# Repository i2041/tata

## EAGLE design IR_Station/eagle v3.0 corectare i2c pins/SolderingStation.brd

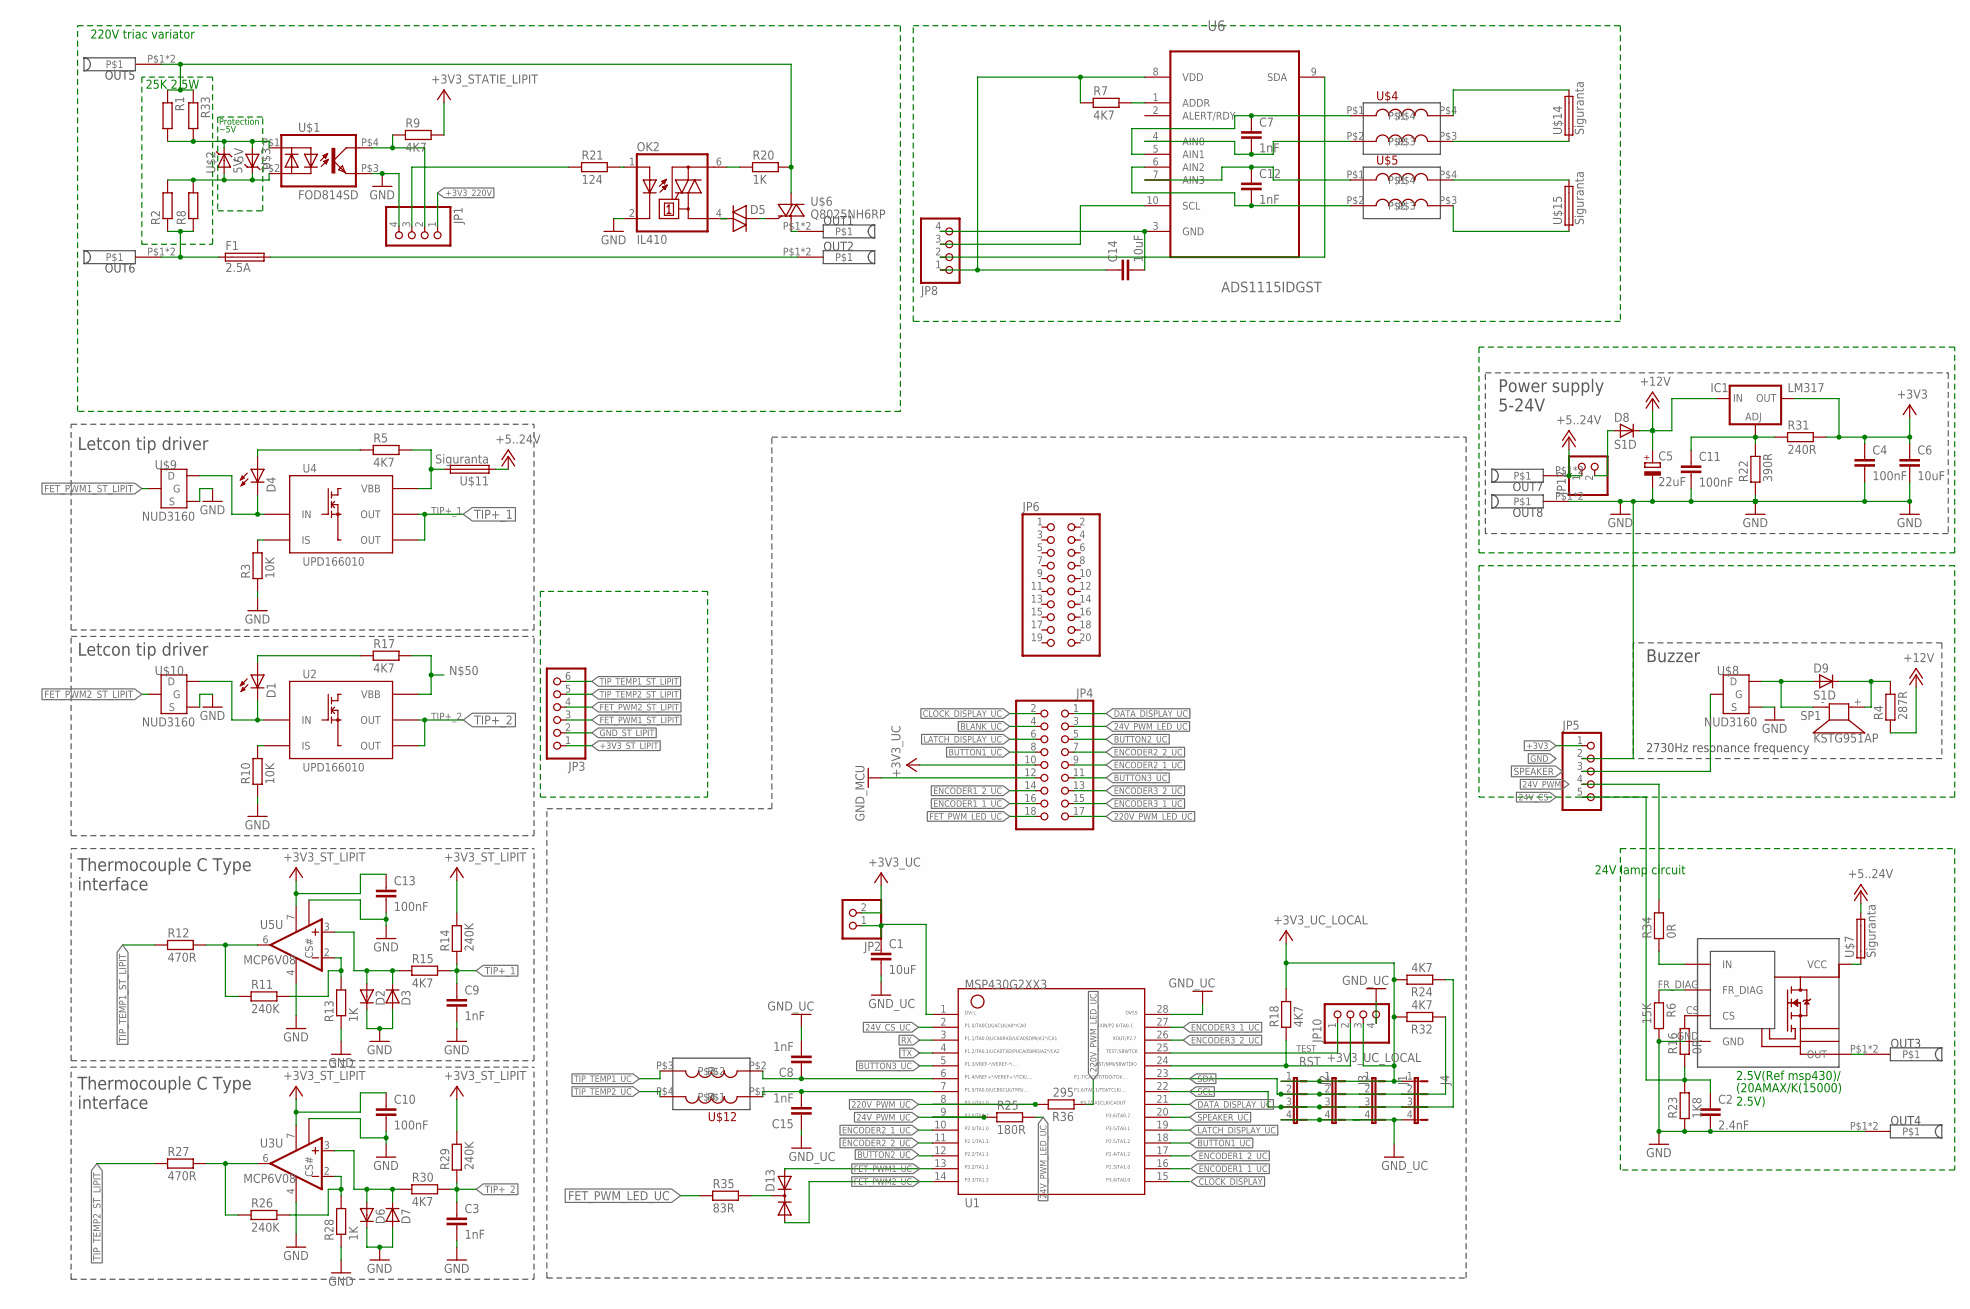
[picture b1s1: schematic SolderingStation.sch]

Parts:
C1, C6: 10uF; 1206
C2: 2.4nF; 0805
C3, C7, C8, C9, C12, C15: 1nF; 0805
C4, C11: 100nF; 1206
C5: 22uF; C_EL_6.3X5.4
C10, C13: 100nF; 0805
C14: 10uF; 0805
CLH1: VN7004; OCTAPAK
D1, D4: LED3MM; LED_3MM
D2, D3, D6, D7: DIODES1D; S1D
D5: DIAC-DO35-10; DO35-10
D8, D9: S1D
D13: DIODE-2AC|CASOT23; SOT23
F1: 2.5A; GSH15
IC1: LM317; DPACK
J1, J2, J3, J4: JP4
JP1, JP8: PINHD-1X4/90; 1X04/90
JP2, JP12: PINHD-1X2; 1X02
JP3: PINHD-1X6/90; 1X06/90
JP4: PINHD-2X9; 2X09
JP5: PINHD-1X5/90; 1X05/90
JP6: PINHD-2X10/90; 2X10/90
JP10: PINHD-1X4; 1X04
OK2: IL410; DIL06
OUT1, OUT2, OUT3, OUT4, OUT5, OUT6, OUT7, OUT8: BANANA
R1, R2, R8, R33: RESISTOR-PTH-0.4; RTH025W
R3, R10: 10K; 0805
R4: 287R; 1206
R5, R7, R15, R17, R18, R24, R30, R32: 4K7; 0805
R6: 15K; 0805
R9: 4K7; 1206
R11, R14, R26, R29: 240K; 0805
R12, R27: 470R; 0805
R13, R28: 1K; 0805
R16, R34: 0R; 0805
R20: 1K; 1206
R21: 124; 1206
R22: 390R; 0805
R23: 1K8; 0805
R25: 180R; 0805
R31: 240R; 0805
R35: 83R; 0805
R36: 295; 1206
SP1: KSTG951AP
U1: MSP340G2443; PW28
U2, U4: UPD166010; TO252-51
U3, U5: MCP6V08; SO08
U6: ADS1115IDGST; SOP50P490X110-10N
U$1: FOD814SD; DIP_4PIN
U$2, U$3: 5V; ZENER
U$4, U$5, U$12: COIL; UNDEF1
U$6: Q8025NH6RP; TO-263
U$7, U$11, U$14, U$15: Siguranta; SOCLU_THERMOCOUPLE
U$8, U$9, U$10: NUD3160; SOT23

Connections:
24V_CS: C2.1, JP5.5, R16.1, R23.2
24V_CS_UC: U1.2
24V_PWM: JP5.4, R34.2
24V_PWM_LED_UC: JP4.3, R25.2
24V_PWM_UC: R25.1, U1.9
220V_PWM_LED_UC: JP4.17, R36.1
220V_PWM_UC: R36.2, U1.8
+3V3: C4.1, C6.1, IC1.4 (OUT), JP5.1, R31.2
+3V3_220V: JP1.1, R9.2
+3V3_ST_LIPIT: C10.1, C13.1, JP3.1, R14.2, R29.2, U3.7 (V+), U5.7 (V+)
+3V3_UC: JP2.2, JP4.10
+3V3_UC_LOCAL: C1.1, J1.1, J2.1, J3.1, J4.1, JP2.1, JP10.3, R18.2, R24.2, R32.2, U1.1
+12V: C5.+, D8.C, IC1.3 (IN), R4.1
+15V: JP12.1, OUT7.P$1, OUT7.P$2, U$7.1B (2), U$7.2B (2), U$11.1A (1), U$11.2A (1)
BLANK_UC: JP4.4
BUTTON1_UC: JP4.8, U1.18
BUTTON2_UC: JP4.5, U1.12
BUTTON3_UC: JP4.11, U1.5
CLOCK_DISPLAY: U1.15
CLOCK_DISPLAY_UC: JP4.2
DATA_DISPLAY_UC: JP4.1, U1.21
ENCODER1_1_UC: JP4.16, U1.16
ENCODER1_2_UC: JP4.14, U1.17
ENCODER2_1_UC: JP4.9, U1.10
ENCODER2_2_UC: JP4.7, U1.11
ENCODER3_1_UC: JP4.15, U1.27
ENCODER3_2_UC: JP4.13, U1.26
FET_PWM1_ST_LIPIT: JP3.3, U$9.1 (G)
FET_PWM1_UC: D13.2 (A2), U1.13
FET_PWM2_ST_LIPIT: JP3.4, U$10.1 (G)
FET_PWM2_UC: D13.1 (A1), U1.14
FET_PWM_LED_UC: JP4.18, R35.1
GND: C2.2, C4.2, C5.-, C6.2, C8.2, C11.2, C15.1, CLH1.GND, J2.4, J3.4, J4.4, JP5.2, OUT4.P$1, OUT4.P$2, OUT8.P$1, OUT8.P$2, R6.2, R22.1, R23.1, U$8.2 (S)
GND_220V: JP1.4, OK2.2 (C), U$1.P$3 (EMIT)
GND_ST_LIPIT: C3.2, C9.2, C10.2, C13.2, D2.C, D3.A, D6.C, D7.A, JP3.2, R3.1, R10.1, R13.1, R28.1, U3.4 (V-), U3.8 (CS#), U5.4 (V-), U5.8 (CS#), U$9.2 (S), U$10.2 (S)
GND_TERMOCOUPLE: C14.2, JP8.4, U6.3 (GND)
GND_UC: C1.2, JP4.12, JP10.4, U1.28
LATCH_DISPLAY_UC: JP4.6, U1.19
unnamed: D1.K (C), U2.2 (IN), U$10.3 (D)
unnamed: D4.A, R5.1
unnamed: D1.A, R17.1
unnamed: D9.A, SP1.- (2), U$8.3 (D)
unnamed: CLH1.CS, R16.2
unnamed: D4.K (C), U4.2 (IN), U$9.3 (D)
unnamed: R10.2, U2.4 (IS)
unnamed: R26.1, R27.2, U3.6 (OUT)
unnamed: D6.A, D7.C, R30.1, U3.3 (+IN)
unnamed: R26.2, R28.2, U3.2 (-IN)
unnamed: OK2.6 (A2), R20.1
unnamed: D5.A (1), OK2.4 (A1)
unnamed: OK2.1 (A), R21.2
unnamed: JP1.3, R21.1
unnamed: CLH1.VCC, U$7.1A (1), U$7.2A (1)
unnamed: D5.C (2), U$6.G
unnamed: D9.C, R4.2, SP1.+ (1)
unnamed: CLH1.FR_DIAG, R6.1
unnamed: F1.1, OUT6.P$1, OUT6.P$2, R2.1, R8.1
unnamed: R3.2, U4.4 (IS)
unnamed: D13.3 (C), R35.2
unnamed: R11.1, R12.2, U5.6 (OUT)
unnamed: R1.2, R33.2, U$1.P$1 (ANODE), U$2.K, U$3.A
unnamed: D2.A, D3.C, R15.1, U5.3 (+IN)
unnamed: R2.2, R8.2, U$1.P$2 (CATHODE), U$2.A, U$3.K
unnamed: R11.2, R13.2, U5.2 (-IN)
unnamed: CLH1.OUTPUT1 (OUT), CLH1.OUTPUT2 (OUT), CLH1.OUTPUT3 (OUT), OUT3.P$1, OUT3.P$2
unnamed: JP1.2, R9.1, U$1.P$4 (COL)
unnamed: C8.1, U1.6, U$12.P$2
unnamed: R7.2, U6.1 (ADDR)
unnamed: C15.2, U1.7, U$12.P$1
unnamed: C7.1, U6.5 (AIN1), U$4.P$1
unnamed: C7.2, U6.4 (AIN0), U$4.P$2
unnamed: C11.1, IC1.1 (ADJ), R22.2, R31.1
unnamed: C12.1, U6.7 (AIN3), U$5.P$1
unnamed: C12.2, U6.6 (AIN2), U$5.P$2
unnamed: CLH1.INPUT (IN), R34.1
unnamed: R5.2, R17.2, U2.TAB (VBB), U4.TAB (VBB), U$11.1B (2), U$11.2B (2)
unnamed: D8.A, JP12.2
unnamed: U$4.P$3, U$14.1A (1), U$14.2A (1)
unnamed: U$4.P$4, U$14.1B (2), U$14.2B (2)
unnamed: U$5.P$4, U$15.1B (2), U$15.2B (2)
unnamed: U$5.P$3, U$15.1A (1), U$15.2A (1)
RST: JP10.2, R18.1, U1.24
RX: U1.3
SCL: J1.3, J2.3, J3.3, J4.3, R24.1, U1.22
SCL_TERMOCOUPLE: JP8.3, U6.10 (SCL)
SDA: J1.2, J2.2, J3.2, J4.2, R32.1, U1.23
SDA_TERMOCOUPLE: JP8.2, U6.9 (SDA)
SPEAKER: JP5.3, U$8.1 (G)
SPEAKER_UC: U1.20
TEST: JP10.1, U1.25
TIP+_1: C9.1, R14.1, R15.2, U4.1 (OUT), U4.5 (OUT)
TIP+_2: C3.1, R29.1, R30.2, U2.1 (OUT), U2.5 (OUT)
TIP_TEMP1_ST_LIPIT: JP3.6, R12.1
TIP_TEMP1_UC: U$12.P$3
TIP_TEMP2_ST_LIPIT: JP3.5, R27.1
TIP_TEMP2_UC: U$12.P$4
TX: U1.4
VCC_TERMOCOUPLE: C14.1, JP8.1, R7.1, U6.8 (VDD)
~+OUT: F1.2, OUT2.P$1, OUT2.P$2
~-OUT: OUT1.P$1, OUT1.P$2, U$6.T1
~IN1: OUT5.P$1, OUT5.P$2, R1.1, R20.2, R33.1, U$6.T2

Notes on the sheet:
Letcon tip driver
Thermocouple C Type
interface
Power supply
5-24V
Buzzer
2730Hz resonance frequency
24V lamp circuit
220V triac variator
25K 2.5W
Protection
~5V
2.5V(Ref msp430)/
(20AMAX/K(15000) 2.5V)

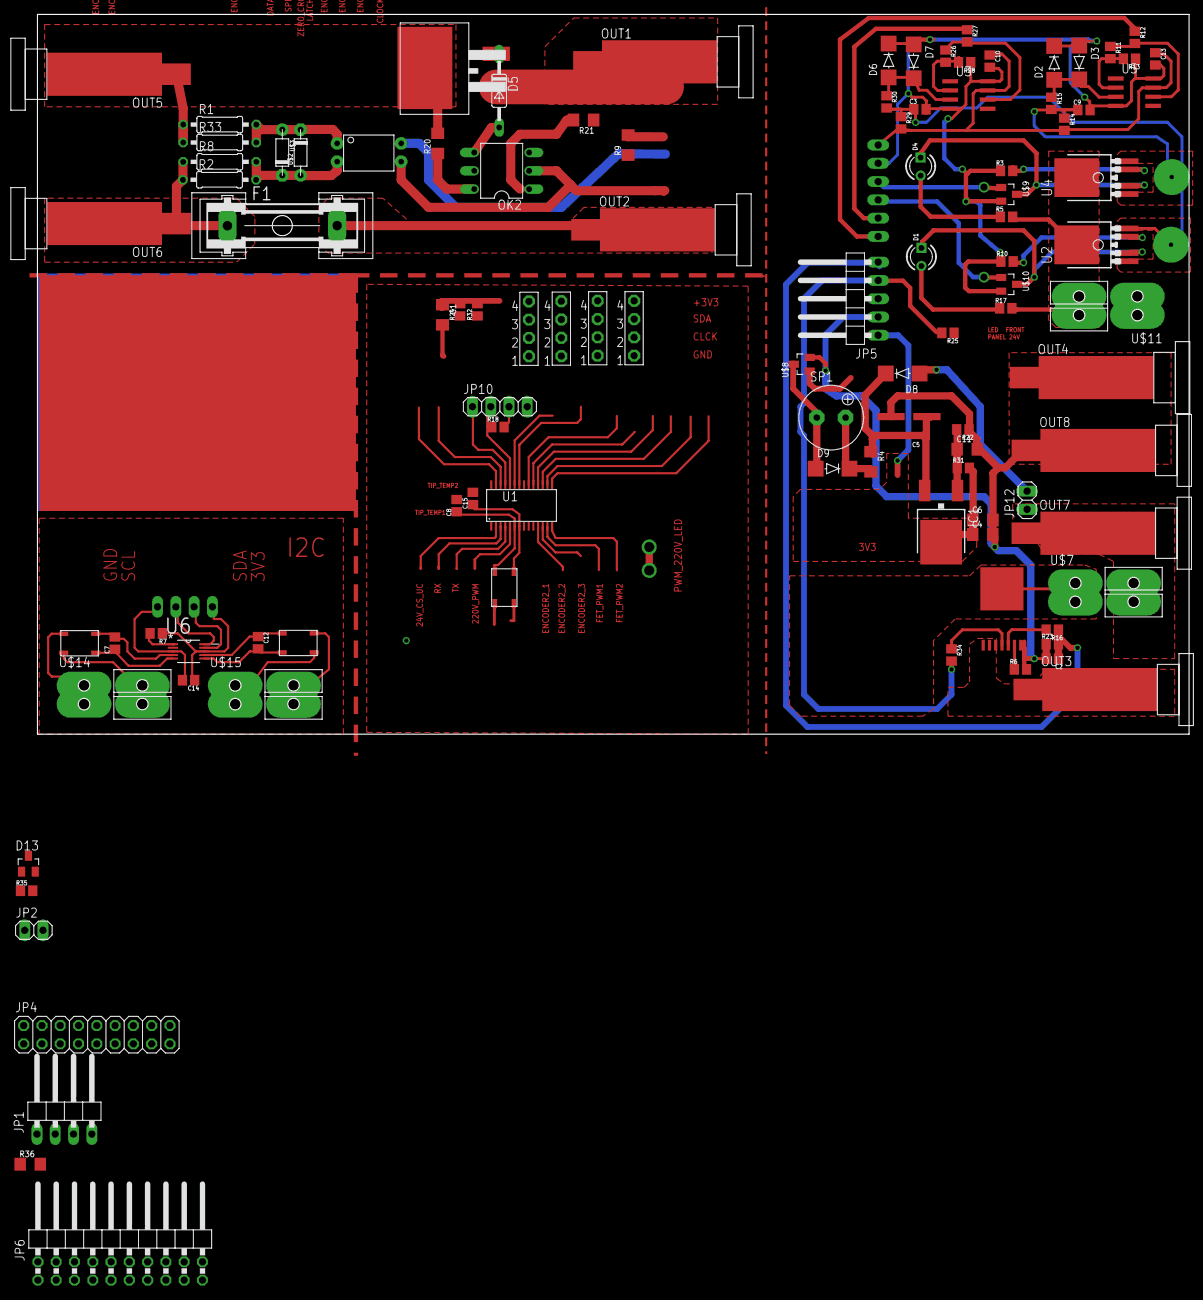
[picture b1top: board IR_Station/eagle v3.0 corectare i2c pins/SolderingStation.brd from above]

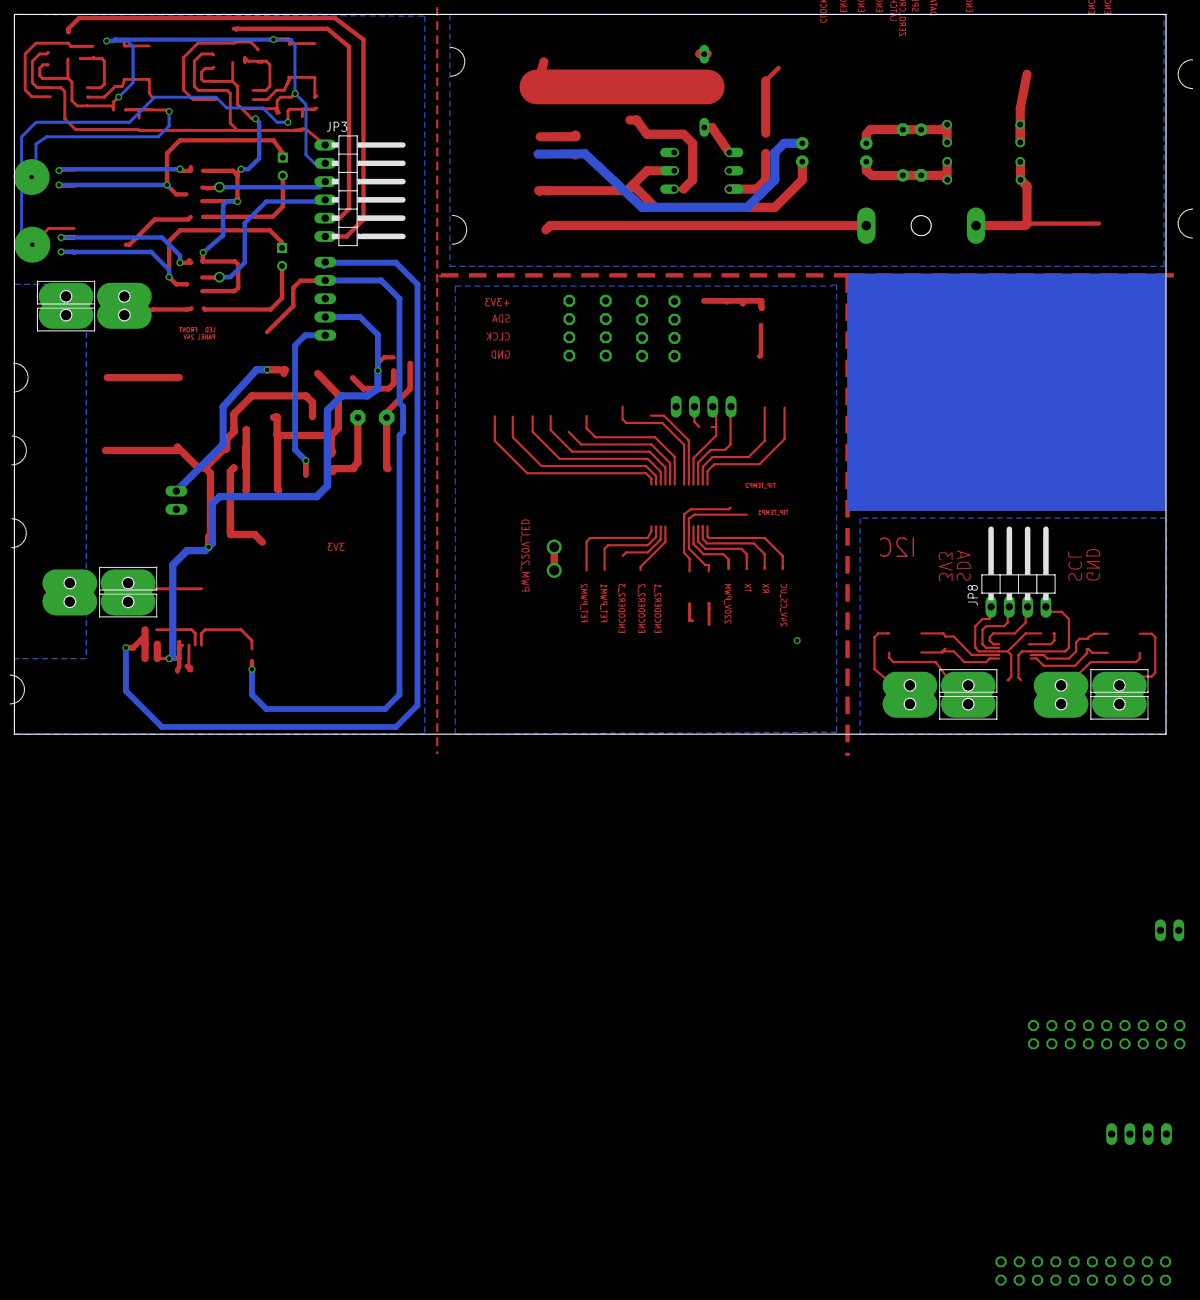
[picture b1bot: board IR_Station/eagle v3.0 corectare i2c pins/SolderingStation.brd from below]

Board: 2 copper layers, 160.0 x 100.0 mm, 106 parts (2 on the bottom side), 92 nets.

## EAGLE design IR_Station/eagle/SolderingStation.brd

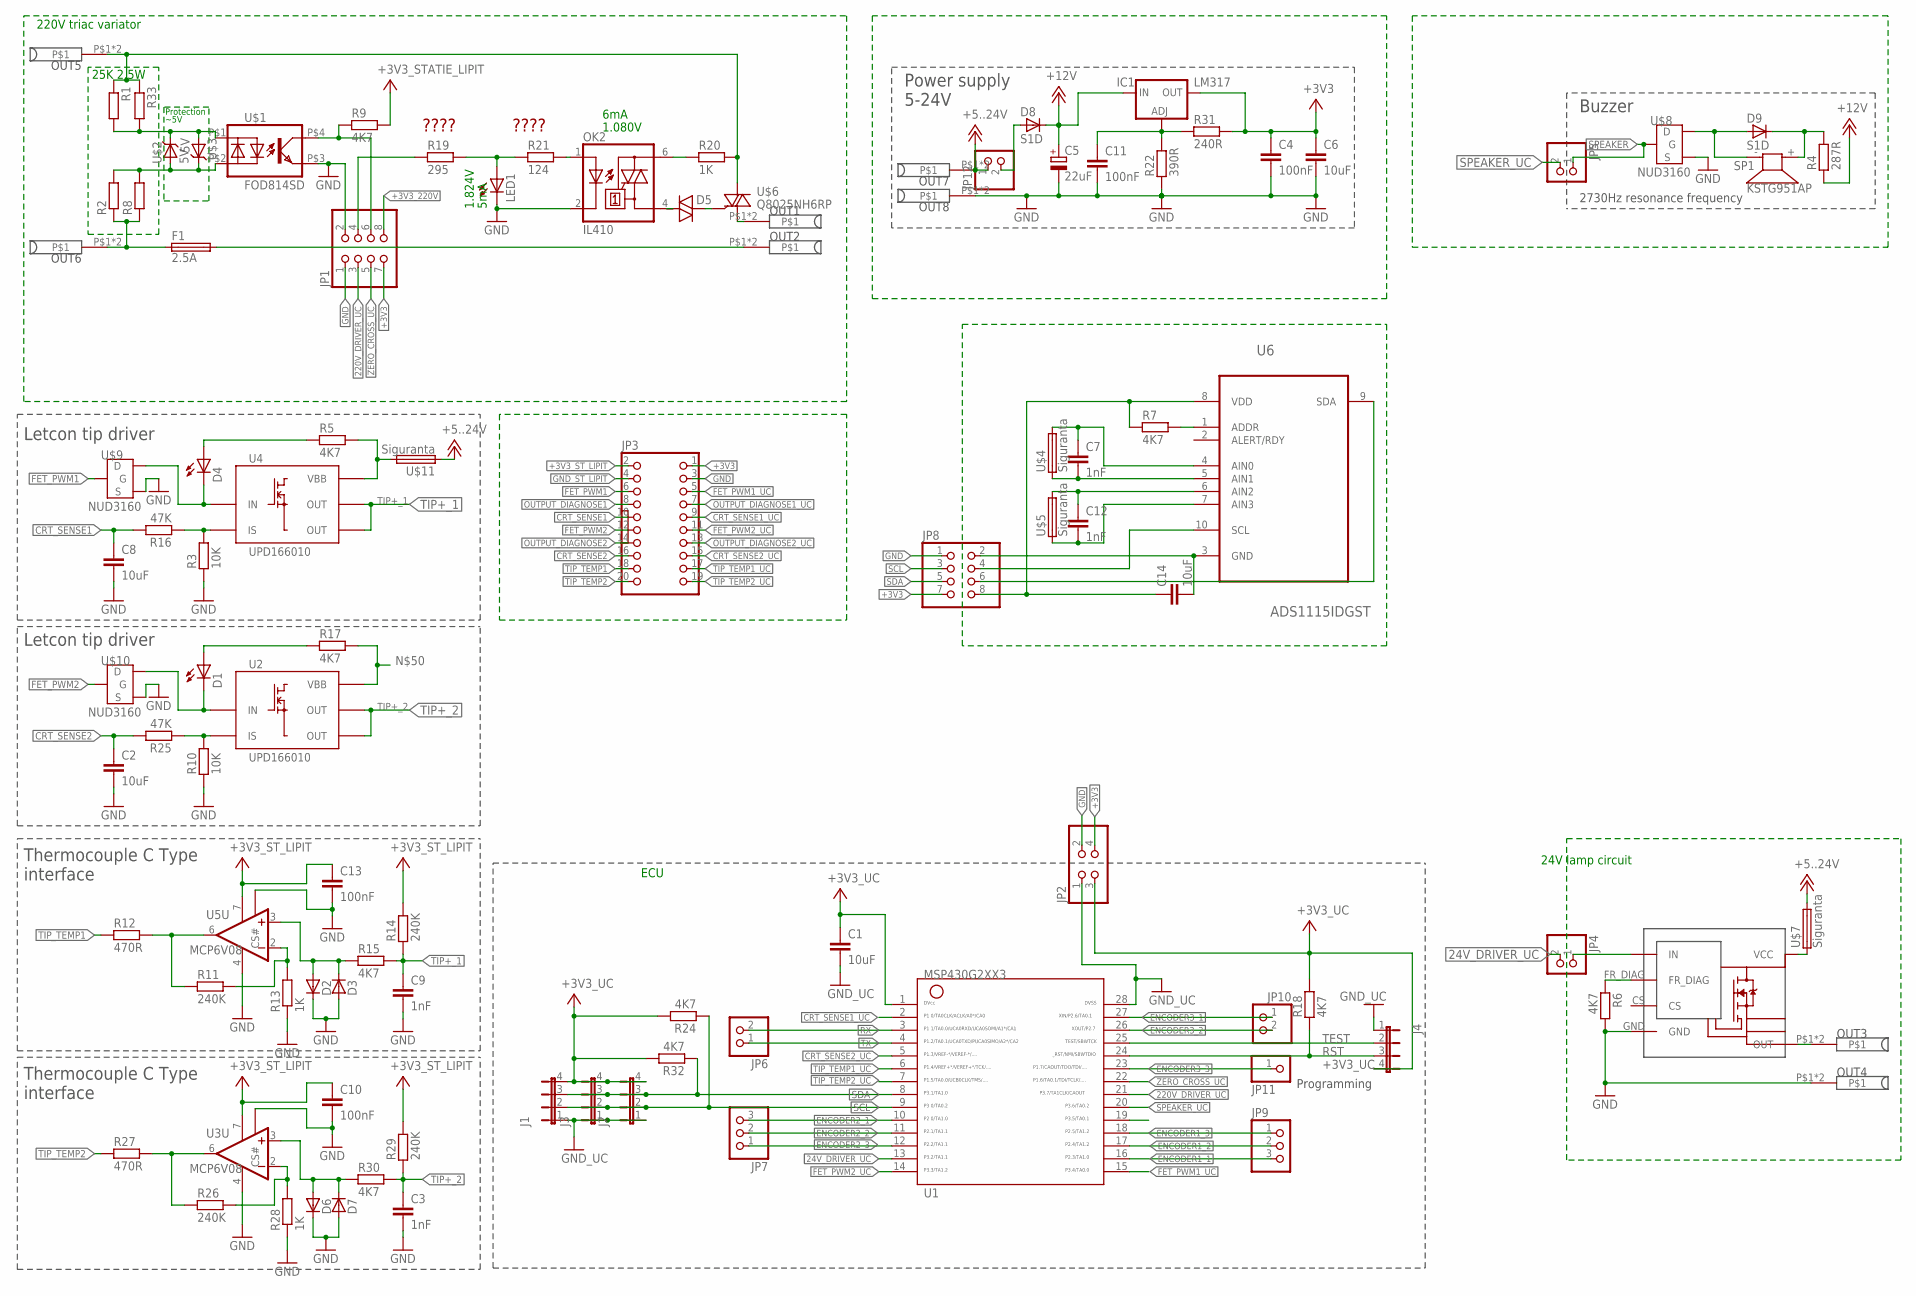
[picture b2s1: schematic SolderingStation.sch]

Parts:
C1, C2, C6, C8: 10uF; 1206
C3, C7, C9, C12: 1nF; 0805
C4, C11: 100nF; 1206
C5: 22uF; C_EL_6.3X5.4
C10, C13: 100nF; 0805
C14: 10uF; 0805
CLH1: VN7004; OCTAPAK
D1, D4: LED3MM; LED_3MM
D2, D3, D6, D7: DIODESOT23; SOT23
D5: DIAC-DO35-10; DO35-10
D8, D9: S1D
F1: 2.5A; GSH15
IC1: LM317; DPACK
J1, J2, J3, J4: JP4
JP1, JP8: PINHD-2X4; 2X04
JP2: PINHD-2X2; 2X02
JP3: PINHD-2X10; 2X10
JP4, JP5, JP6, JP10, JP12: PINHD-1X2; 1X02
JP7, JP9: PINHD-1X3; 1X03
JP11: PINHD-1X1; 1X01
LED1: LEDCHIPLED_0603; CHIPLED_0603
OK2: IL410; DIL06
OUT1, OUT2, OUT3, OUT4, OUT5, OUT6, OUT7, OUT8: BANANA
R1, R2, R8, R33: RESISTOR-PTH-0.4; RTH025W
R3, R10: 10K; 0805
R4: 287R; 1206
R5, R6, R7, R15, R17, R18, R24, R30, R32: 4K7; 0805
R9: 4K7; 1206
R11, R14, R26, R29: 240K; 0805
R12, R27: 470R; 0805
R13, R28: 1K; 0805
R16, R25: 47K; 0805
R19: 295; 1206
R20: 1K; 1206
R21: 124; 1206
R22: 390R; 0805
R31: 240R; 0805
SP1: KSTG951AP
U1: MSP340G2443; PW28
U2, U4: UPD166010; TO252-51
U3, U5: MCP6V08; SO08
U6: ADS1115IDGST; SOP50P490X110-10N
U$1: FOD814SD; DIP_4PIN
U$2, U$3: 5V; ZENER
U$4, U$5, U$7, U$11: Siguranta; SOCLU_THERMOCOUPLE
U$6: Q8025NH6RP; TO-263
U$8, U$9, U$10: NUD3160; SOT23

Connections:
24V_DRIVER_UC: JP4.2, U1.13
220V_DRIVER_UC: JP1.3, U1.21
+3V3: C4.1, C6.1, IC1.4 (OUT), J1.4, J2.4, J3.4, JP1.7, JP2.4, JP3.1, JP8.7, R24.2, R31.2, R32.2
+3V3_220V: JP1.8, R9.2
+3V3_CONTROLLER: C1.1, U1.1
+3V3_ST_LIPIT: C10.1, C13.1, JP3.2, R14.2, R29.2, U3.7 (V+), U5.7 (V+)
+3V3_UC: J4.4, JP2.3, R18.2
+12V: C5.+, D8.C, IC1.3 (IN), R4.1
+15V: JP12.1, OUT7.P$1, OUT7.P$2, U$7.1B (2), U$7.2B (2), U$11.1A (1), U$11.2A (1)
CRT_SENSE1: C8.1, JP3.10, R16.2
CRT_SENSE1_UC: JP3.9, U1.2
CRT_SENSE2: C2.1, JP3.16, R25.2
CRT_SENSE2_UC: JP3.15, U1.5
ENCODER1_1: JP9.3, U1.16
ENCODER1_2: JP9.2, U1.17
ENCODER1_3: JP9.1, U1.18
ENCODER2_1: JP7.3, U1.10
ENCODER2_2: JP7.2, U1.11
ENCODER2_3: JP7.1, U1.12
ENCODER3_1: JP10.1, U1.27
ENCODER3_2: JP10.2, U1.26
ENCODER3_3: JP11.1, U1.23
FET_PWM1: JP3.6, U$9.1 (G)
FET_PWM1_UC: JP3.5, U1.15
FET_PWM2: JP3.12, U$10.1 (G)
FET_PWM2_UC: JP3.11, U1.14
GND: C4.2, C5.-, C6.2, C11.2, CLH1.GND, J1.1, J2.1, J3.1, JP1.1, JP2.2, JP3.3, JP8.1, OUT4.P$1, OUT4.P$2, OUT8.P$1, OUT8.P$2, R6.2, R22.1, U$8.2 (S)
GND_220V: JP1.2, LED1.C, OK2.2 (C), U$1.P$3 (EMIT)
GND_ST_LIPIT: C2.2, C3.2, C8.2, C9.2, C10.2, C13.2, D2.3 (C), D3.1 (A), D6.3 (C), D7.1 (A), JP3.4, R3.1, R10.1, R13.1, R28.1, U3.4 (V-), U3.8 (CS#), U5.4 (V-), U5.8 (CS#), U$9.2 (S), U$10.2 (S)
GND_UC: C1.2, J4.1, JP2.1, U1.28
unnamed: D1.K (C), U2.2 (IN), U$10.3 (D)
unnamed: D4.A, R5.1
unnamed: D1.A, R17.1
unnamed: D9.A, SP1.- (2), U$8.3 (D)
unnamed: D4.K (C), U4.2 (IN), U$9.3 (D)
unnamed: R10.2, R25.1, U2.4 (IS)
unnamed: R26.1, R27.2, U3.6 (OUT)
unnamed: D6.1 (A), D7.3 (C), R30.1, U3.3 (+IN)
unnamed: R26.2, R28.2, U3.2 (-IN)
unnamed: OK2.6 (A2), R20.1
unnamed: D5.A (1), OK2.4 (A1)
unnamed: OK2.1 (A), R21.2
unnamed: JP1.4, R19.1
unnamed: CLH1.VCC, U$7.1A (1), U$7.2A (1)
unnamed: LED1.A, R19.2, R21.1
unnamed: D5.C (2), U$6.G
unnamed: D9.C, R4.2, SP1.+ (1)
unnamed: CLH1.FR_DIAG, R6.1
unnamed: F1.1, OUT6.P$1, OUT6.P$2, R2.1, R8.1
unnamed: CLH1.INPUT (IN), JP4.1
unnamed: R3.2, R16.1, U4.4 (IS)
unnamed: R11.1, R12.2, U5.6 (OUT)
unnamed: R1.2, R33.2, U$1.P$1 (ANODE), U$2.K, U$3.A
unnamed: D2.1 (A), D3.3 (C), R15.1, U5.3 (+IN)
unnamed: R2.2, R8.2, U$1.P$2 (CATHODE), U$2.A, U$3.K
unnamed: R11.2, R13.2, U5.2 (-IN)
unnamed: CLH1.OUTPUT1 (OUT), CLH1.OUTPUT2 (OUT), CLH1.OUTPUT3 (OUT), OUT3.P$1, OUT3.P$2
unnamed: JP1.6, R9.1, U$1.P$4 (COL)
unnamed: C14.2, JP8.2, U6.3 (GND)
unnamed: R7.2, U6.1 (ADDR)
unnamed: C14.1, JP8.8, R7.1, U6.8 (VDD)
unnamed: C7.1, U6.4 (AIN0), U$4.1B (2), U$4.2B (2)
unnamed: C7.2, U6.5 (AIN1), U$4.1A (1), U$4.2A (1)
unnamed: C11.1, IC1.1 (ADJ), R22.2, R31.1
unnamed: C12.1, U6.6 (AIN2), U$5.1B (2), U$5.2B (2)
unnamed: C12.2, U6.7 (AIN3), U$5.1A (1), U$5.2A (1)
unnamed: JP8.4, U6.10 (SCL)
unnamed: JP8.6, U6.9 (SDA)
unnamed: R5.2, R17.2, U2.TAB (VBB), U4.TAB (VBB), U$11.1B (2), U$11.2B (2)
unnamed: D8.A, JP12.2
OUTPUT_DIAGNOSE1: JP3.8
OUTPUT_DIAGNOSE1_UC: JP3.7
OUTPUT_DIAGNOSE2: JP3.14
OUTPUT_DIAGNOSE2_UC: JP3.13
RST: J4.3, R18.1, U1.24
RX: JP6.2, U1.3
SCL: J1.2, J2.2, J3.2, JP8.3, R24.1, U1.9
SDA: J1.3, J2.3, J3.3, JP8.5, R32.1, U1.8
SEGMENT_D: U1.19
SPEAKER: JP5.1, U$8.1 (G)
SPEAKER_UC: JP5.2, U1.20
TEST: J4.2, U1.25
TIP+_1: C9.1, R14.1, R15.2, U4.1 (OUT), U4.5 (OUT)
TIP+_2: C3.1, R29.1, R30.2, U2.1 (OUT), U2.5 (OUT)
TIP_TEMP1: JP3.18, R12.1
TIP_TEMP1_UC: JP3.17, U1.6
TIP_TEMP2: JP3.20, R27.1
TIP_TEMP2_UC: JP3.19, U1.7
TX: JP6.1, U1.4
ZERO_CROSS_UC: JP1.5, U1.22
~+OUT: F1.2, OUT2.P$1, OUT2.P$2
~-OUT: OUT1.P$1, OUT1.P$2, U$6.T1
~IN1: OUT5.P$1, OUT5.P$2, R1.1, R20.2, R33.1, U$6.T2

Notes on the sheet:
Programming
Letcon tip driver
Thermocouple C Type
interface
Power supply
5-24V
Buzzer
2730Hz resonance frequency
24V lamp circuit
220V triac variator
ECU
25K 2.5W
Protection
~5V
????
1.080V
1.824V
6mA
5mA

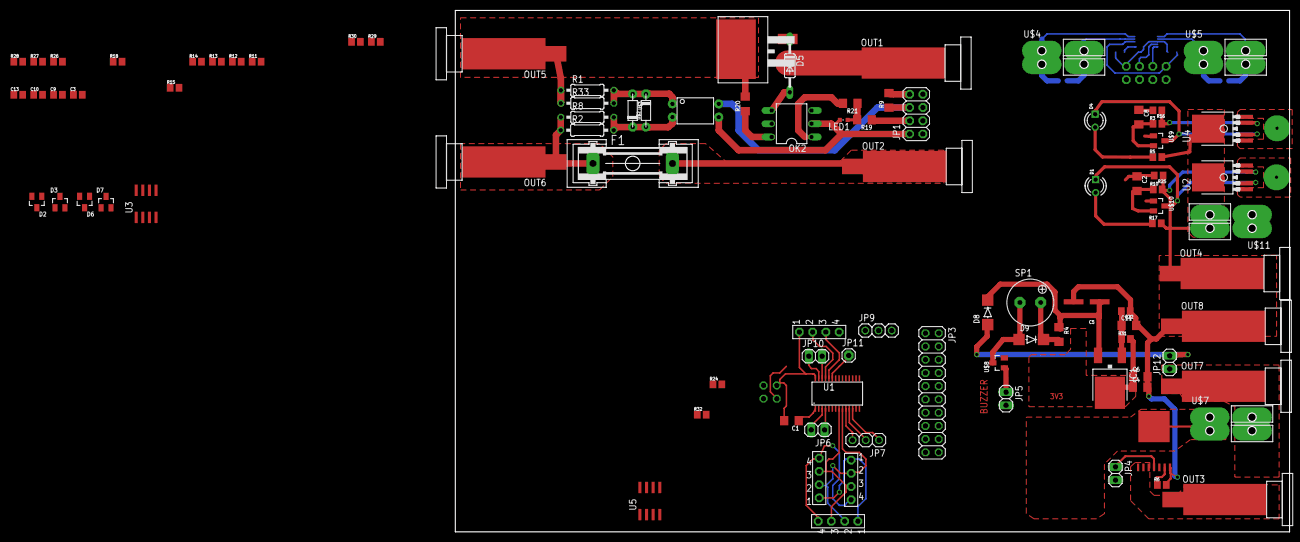
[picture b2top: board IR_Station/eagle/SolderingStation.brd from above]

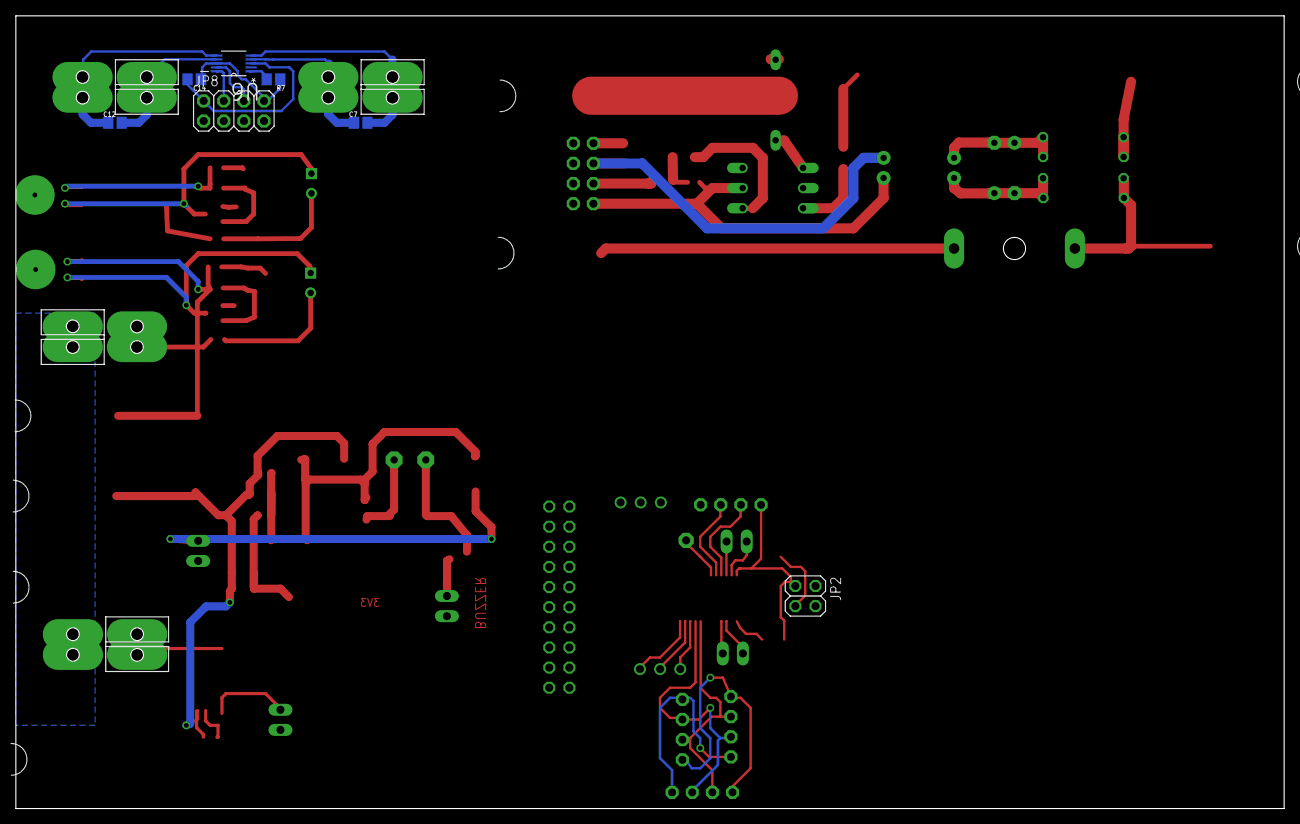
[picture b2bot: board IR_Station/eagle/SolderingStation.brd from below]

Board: 2 copper layers, 160.0 x 100.0 mm, 102 parts (7 on the bottom side), 88 nets.

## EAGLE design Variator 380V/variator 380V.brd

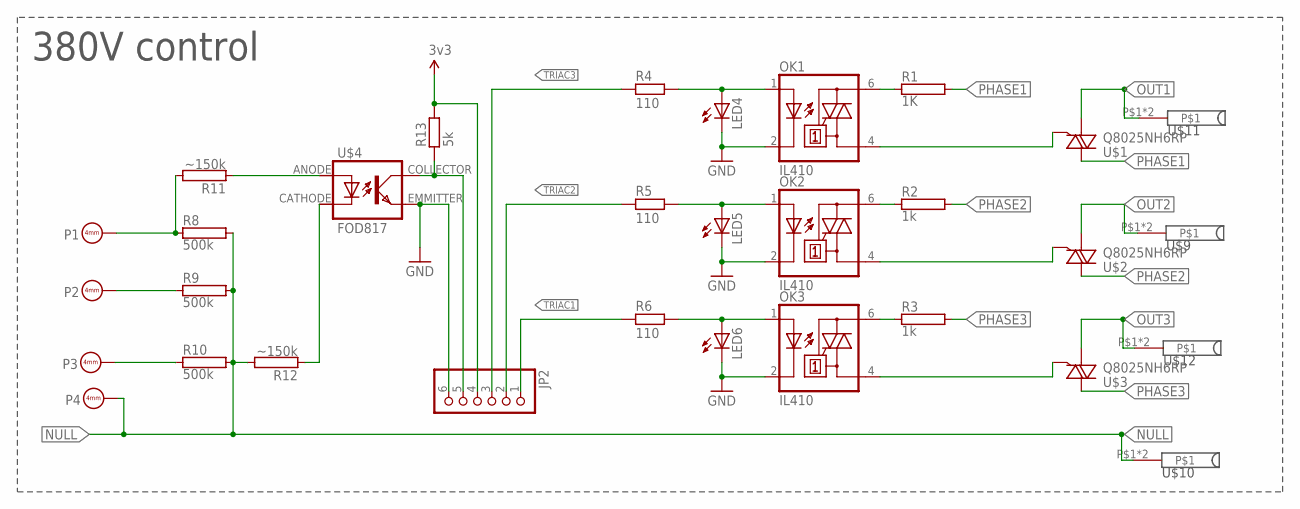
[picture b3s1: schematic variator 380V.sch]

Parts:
JP2: PINHD-1X6/90; 1X06/90
LED4, LED5, LED6: LED5MM
OK1, OK2, OK3: IL410; DIL06
P1, P2, P3, P4: BANANA
R1: 1K; HPS58
R2, R3: 1k; HPS58
R4, R5, R6: 110; 1206
R8, R9, R10: 500k; AC01
R11, R12: ~150k; HPS58
R13: 5k; 1206
U$1, U$2, U$3: Q8025NH6RP; TO-263
U$4: FOD817; FOD_4PIN
U$9, U$10, U$11, U$12: BANANA

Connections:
3V3: JP2.4, R13.2
GND: JP2.6, LED4.K (C), LED5.K (C), LED6.K (C), OK1.2 (C), OK2.2 (C), OK3.2 (C), U$4.EMMITTER (EMIT)
unnamed: OK2.4 (A1), U$2.G
unnamed: OK1.4 (A1), U$1.G
unnamed: OK3.4 (A1), U$3.G
unnamed: OK1.6 (A2), R1.1
unnamed: OK2.6 (A2), R2.1
unnamed: OK3.6 (A2), R3.1
unnamed: LED4.A, OK1.1 (A), R4.2
unnamed: LED5.A, OK2.1 (A), R5.2
unnamed: LED6.A, OK3.1 (A), R6.2
unnamed: R12.1, U$4.CATHODE
unnamed: R11.1, U$4.ANODE
unnamed: JP2.5, R13.1, U$4.COLLECTOR (COL)
NULL: P4.P$1, R8.2, R9.2, R10.2, R12.2, U$10.P$1, U$10.P$2
OUT1: U$1.T1, U$11.P$1, U$11.P$2
OUT2: U$2.T1, U$9.P$1, U$9.P$2
OUT3: U$3.T1, U$12.P$1, U$12.P$2
PHASE1: P1.P$1, R1.2, R8.1, R11.2, U$1.T2
PHASE2: P2.P$1, R2.2, R9.1, U$2.T2
PHASE3: P3.P$1, R3.2, R10.1, U$3.T2
TRIAC1: JP2.1, R6.1
TRIAC2: JP2.2, R5.1
TRIAC3: JP2.3, R4.1

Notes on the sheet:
380V control

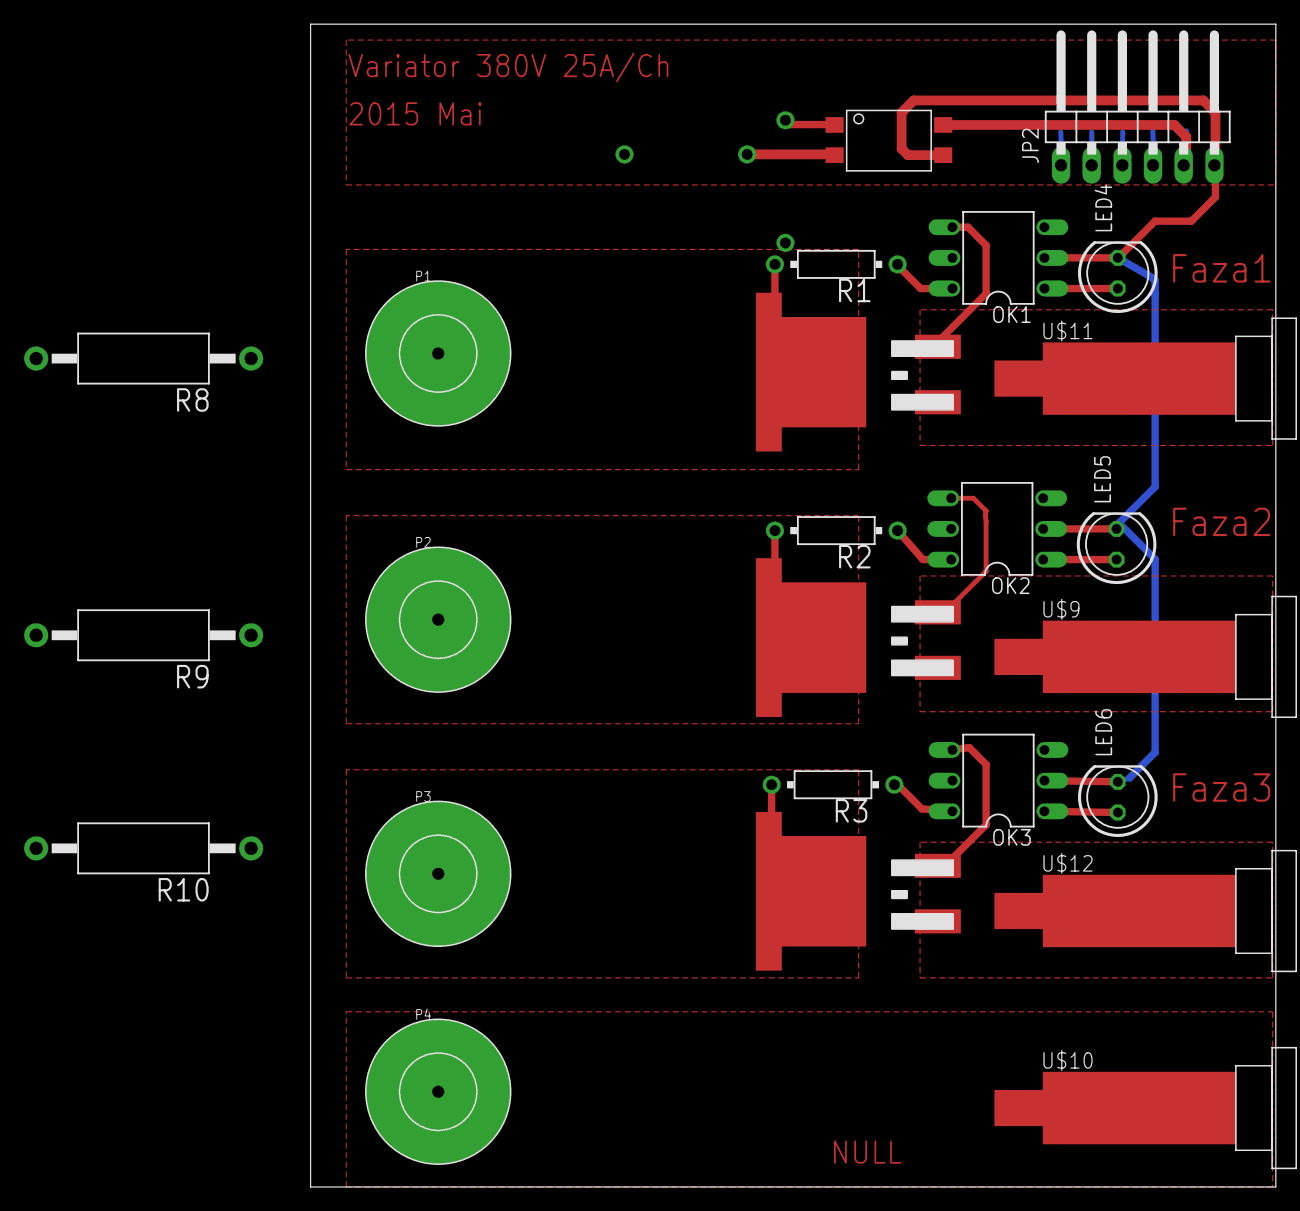
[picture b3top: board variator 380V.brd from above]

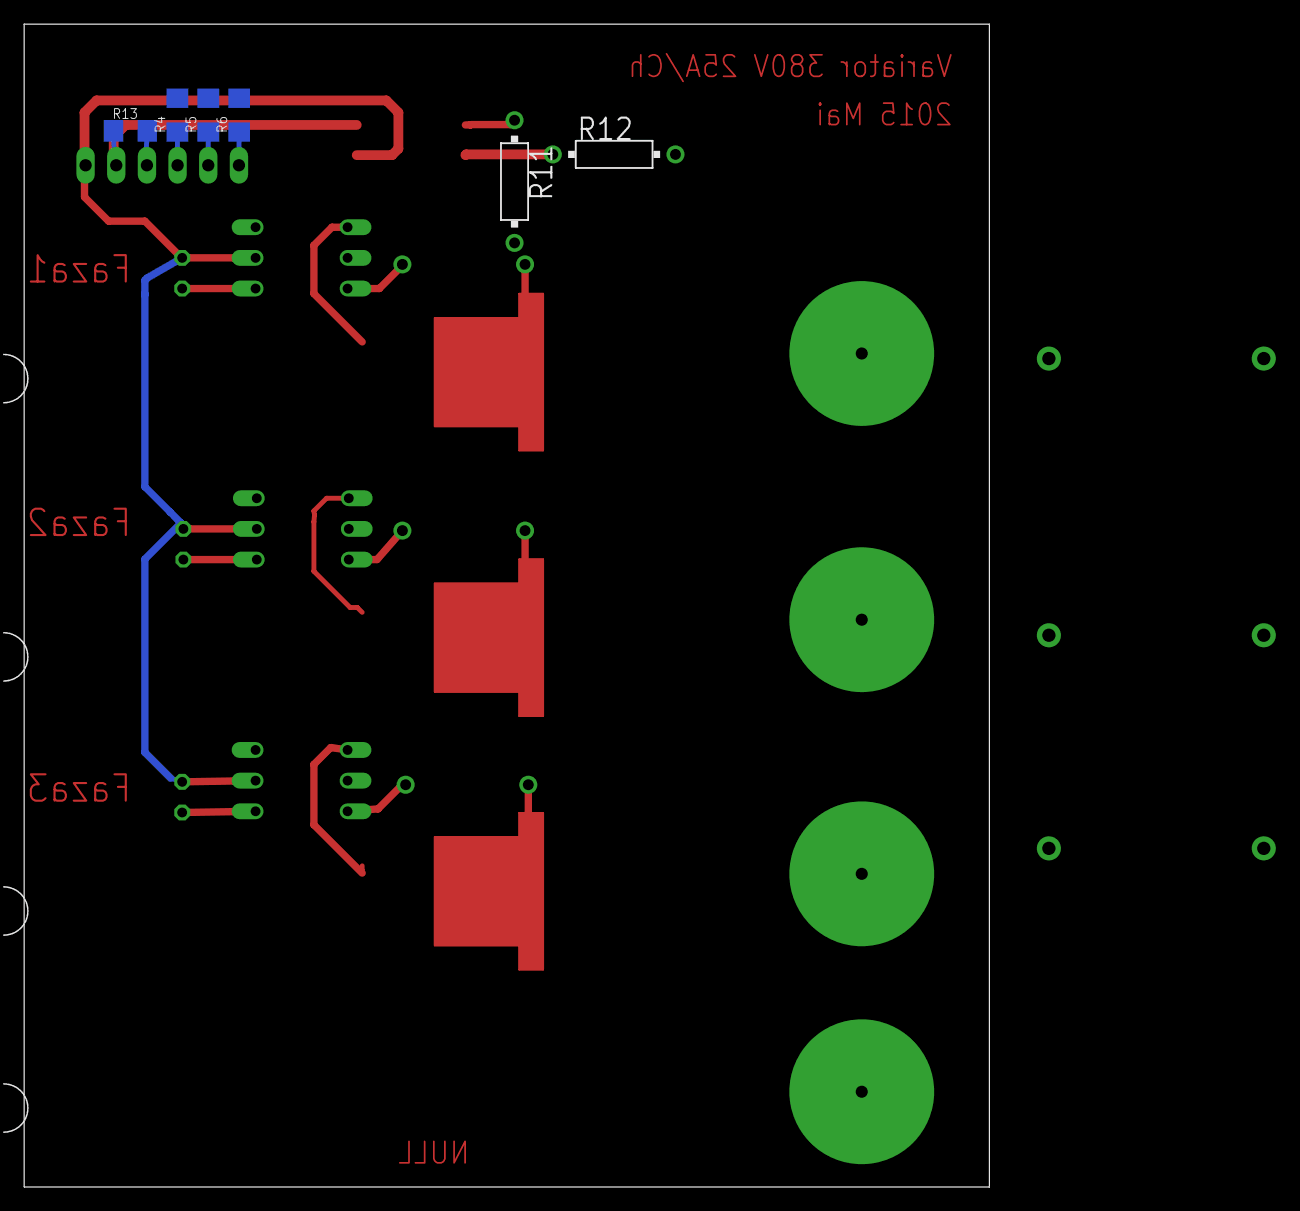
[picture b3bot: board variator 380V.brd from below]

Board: 2 copper layers, 80.0 x 96.3 mm, 31 parts (6 on the bottom side), 24 nets.

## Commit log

2015-02-08 test file commit
2015-02-08 SePl: commit all project
2015-02-08 SePl: delete test file
2015-02-08 SePl: return voltage implementation
2015-02-08 test ignore lists
2015-02-08 interval comment for commontypes.h
2015-02-08 adaugare metode wakeup si go to sleep si modificari in metoda de read InternalTemperature
2015-02-08 am adaugat file viktor
2015-02-08 am sters file viktor
2015-02-12 implementare in sleep mode si in wakeUp mode de la button
2015-02-15 15.02.2015 reusit totul
2015-02-15 implementare eroare cu 2 retryers
2015-02-15 define for activeButtonForReset
2015-02-16 separate retry for mode3
2015-02-16 implement error for couple
2015-02-20 change wakeup on falling edge
2015-02-21 implement error for Voltage and lowVoltage
2015-03-19 avion aerofoil
2015-05-11 Correct Triac Supply
2015-06-28 aripa intreaga prima incercare
2015-06-30 corectare asamblare si sustinere aripa vertical
2015-09-15 - incercare corectare aprindere nereusita trebuie de verificat!!
2015-09-15 change comment
2015-10-19 stergerea valorilor externe prin includerea headerelor inlocuirea potTimpului cu maxTemperature adaugarea durata de lucru de 30 minute
2015-10-22 Noua implementare a state masinei Am schimbat state masina, am adaugat stare pentru a raci camera
2015-10-24 corectare temperatura maxima nu facem initializarea daca e active mode temperatura minima de racire la 40 grade
2015-10-24 implementare watchDog !!!!!!!! Trebuie de Verificat !!!!!!!
2015-12-03 IR_Station
2015-12-11 ads1115 i2c First implementation
2015-12-14 Implemented successful I2C and tested.
2015-12-14 Multiplexing method to Configure register for each PIN. Example: to read pin 0 need to configure register for pin 0, after read conversion register.
2015-12-23 implementare CRC, infrarosu sensor
2015-12-29 Implementation WatchDog timer interrupt
2015-12-29 final project need to test!!
2015-12-30 Update linse from all pins! some features :)
2015-12-30 PDF, and correct few lines.
2015-12-30 PDF, and correct text lines
2016-01-02 implementation to print on console general function print(%d %f %c % *c) MLX90614 read function change with add parameter for read what you need
2016-01-04 TLC5947 implementare
2016-01-05 implementare TLC5947 pentru updatarea displaiului si calcularea digitilor
2016-01-15 implementation driver for 220V and Ciocane de lipit !!!!!!!!!!!!!!!!!need to test!!!!!!!!!!!!!!!!!!!!!!
2016-01-23 last changes
2016-01-25 corectare timer init la statia de lipit
2016-01-29 Implementare algoritm for Ciocan lipit need to test if thermocouple is update corectly
2016-01-31 AVG set 25 implementation ADC set flag for 33ms task Method for thermocouple ADC to Temperature
2016-01-31 Adi program for station soldering
2016-02-04 implementare ciocan lipit alghoritm.
2016-02-04 tuning for ciocan de lipit inversare PWM1 cu PWM2
2016-02-14 corectare printf implementare 220V algoritm implementare 24V algoritm
2016-02-14 last updates manual setting PWM on 24V on 220V need to test implementation
2016-02-14 _ciocanLipit_defaultTemperature = 260 degrees Celsius adapting state for can detect state for ciocan lipit
2016-02-15 update print function update the ciocan de lipit notification state
2016-02-18 pre-implementation 24V and 220V alghoritm
2016-02-18 implementation 25V and 220V, TESTED
2016-02-22 testare 220V si 24V algoritm merge bine dar trebuie de modificat implementarea algoritmului 220V.c
2018-04-04 04.04.2018

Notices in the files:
parts and their libraries:
SparkFun-Aesthetics: Licensing: Creative Commons ShareAlike 4.0 International - https://creativecommons.org/licenses/by-sa/4.0
